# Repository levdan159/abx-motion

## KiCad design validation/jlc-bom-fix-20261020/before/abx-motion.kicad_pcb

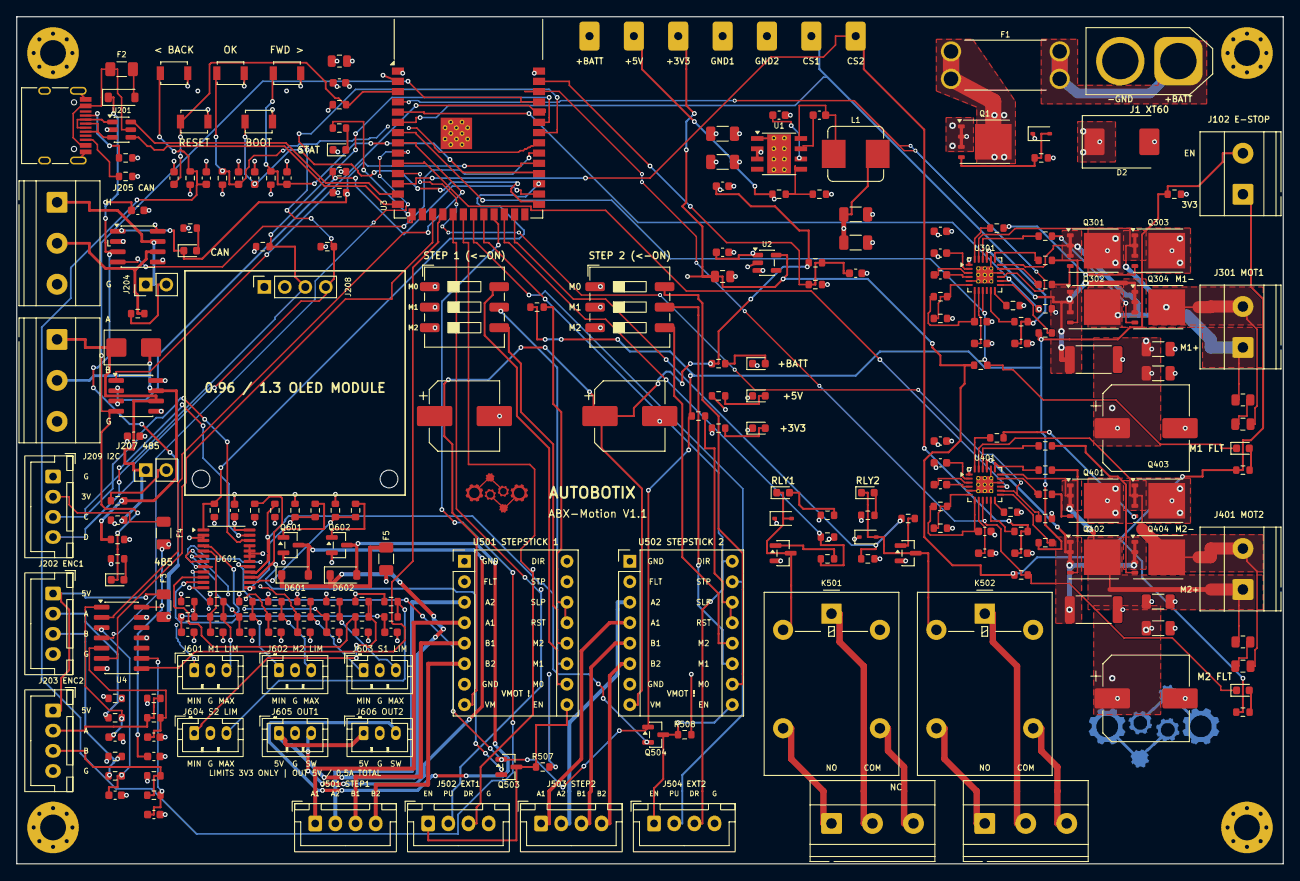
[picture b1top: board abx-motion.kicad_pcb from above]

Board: 4 copper layers, 157.0 x 105.0 mm, 250 parts (1 on the bottom side), 174 nets.

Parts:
C1, C4, C6, C202, C203, C204, C209, C210, C211, C212, C213, C214, C302, C309, C402, C409, C601: 100nF; C_0603_1608Metric
C2, C3, C307, C308, C407, C408: 4.7uF; C_1206_3216Metric
C5, C9, C301, C303, C304, C401, C403, C404: 1uF; C_0603_1608Metric
C7, C8: 22uF; C_1206_3216Metric
C10, C201: 10uF; C_0805_2012Metric
C205, C206, C207, C208: 1nF; C_0603_1608Metric
C305, C405, C602, C603, C604, C605, C606, C607, C608, C609: 10nF; C_0603_1608Metric
C306, C406: 220uF; CP_Elec_10x10.5
C310, C410: 2.2nF; C_0805_2012Metric
C501, C502: 100uF; CP_Elec_8x10.5
D1: BZT52C12S; D_SOD-323
D2: SMCJ30A; D_SMC
D201: SMBJ6.5CA; D_SMB
D202, D601, D602: B5819W; D_SOD-123
D501, D503: 1N4148WS; D_SOD-323
D502, D504: LED_GRN; LED_0603_1608Metric
F1: 25A; Fuseholder_Keystone_3557-2
F2, F3: 500mA_PTC; Fuse_1206_3216Metric
F4: 250mA_PTC; Fuse_1206_3216Metric
F5: 1206L050/15YR; Fuse_1206_3216Metric
H1, H2, H3, H4: M3_Mount; MountingHole_3.2mm_M3_Pad_Via
H5, H6: M2_OLED; MountingHole_2.2mm_M2
J1: XT60_BAT; AMASS_XT60-M_1x02_P7.20mm_Vertical
J102: E_STOP; TerminalBlock_Phoenix_MKDS-1,5-2-5.08_1x02_P5.08mm_Horizont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
J201: USB-C; USB_C_Receptacle_HRO_TYPE-C-31-M-12
J202: ENC1_CONN; JST_XH_B4B-XH-A_1x04_P2.50mm_Vertical
J203: ENC2_CONN; JST_XH_B4B-XH-A_1x04_P2.50mm_Vertical
J204: CAN_TERM; PinHeader_1x02_P2.54mm_Vertical
J205: CAN_BUS; TerminalBlock_Phoenix_MKDS-1,5-3-5.08_1x03_P5.08mm_Horizont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
J206: RS485_TERM; PinHeader_1x02_P2.54mm_Vertical
J207: RS485_BUS; TerminalBlock_Phoenix_MKDS-1,5-3-5.08_1x03_P5.08mm_Horizont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
J208: OLED_I2C; PinSocket_1x04_P2.54mm_Vertical
J209: I2C_EXP; JST_XH_B4B-XH-A_1x04_P2.50mm_Vertical
J301, J401: MOTOR_OUT; TerminalBlock_Phoenix_MKDS-1,5-2-5.08_1x02_P5.08mm_Horizont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
J501: STEP1_MOTOR; JST_XH_B4B-XH-A_1x04_P2.50mm_Vertical
J502: STEP1_EXT; JST_XH_B4B-XH-A_1x04_P2.50mm_Vertical
J503: STEP2_MOTOR; JST_XH_B4B-XH-A_1x04_P2.50mm_Vertical
J504: STEP2_EXT; JST_XH_B4B-XH-A_1x04_P2.50mm_Vertical
J505: RELAY1_OUT; TerminalBlock_Phoenix_MKDS-1,5-3-5.08_1x03_P5.08mm_Horizont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
J506: RELAY2_OUT; TerminalBlock_Phoenix_MKDS-1,5-3-5.08_1x03_P5.08mm_Horizont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
J601, J602, J603, J604, J605, J606: B3B-PH-K-S; JST_PH_B3B-PH-K_1x03_P2.00mm_Vertical
K501, K502: G5LE-14-DC5; Relay_SPDT_Omron-G5LE-1
L1: 15uH; L_Bourns_SRP7028A_7.3x6.6mm
LED201: LED_YEL_CAN; LED_0603_1608Metric
LED202: LED_YEL_485; LED_0603_1608Metric
LED203: LED_BLU_STAT; LED_0603_1608Metric
LED_FLT1, LED_FLT2: LED_RED_FLT; LED_0603_1608Metric
LED_PWR_3V3_1, LED_PWR_5V1: LED_GRN; LED_0603_1608Metric
LED_PWR_BATT1: LED_GRN; LED_0603_1608Metric
LOGO1: ABX_Logo_Gears_Gold
LOGO2: ABX_Text_Gold
Q1: SQJ459EP-T1_GE3; TDSON-8-1
Q301, Q302, Q303, Q304, Q401, Q402, Q403, Q404: CSD18540Q5B; TDSON-8-1
Q501, Q502, Q503, Q504, Q601, Q602: AO3400A; SOT-23
R1: 47k; R_0603_1608Metric
R2, R4: 100k; R_0603_1608Metric
R3, R6, R9, R203, R204, R205, R206, R207, R208, R209, R210, R227, R228, R229, R231, R232, R303, R403, R505, R506, R507, R508, R621, R622: 10k; R_0603_1608Metric
R5: 24.9k; R_0603_1608Metric
R7, R8, R212, R214, R216, R218, R220, R224, R230, R304, R311, R404, R411, R502, R504, R609, R610, R611, R612, R613, R614, R615, R616, R617, R618: 1k; R_0603_1608Metric
R201, R202: 5.1k; R_0603_1608Metric
R211, R213, R215, R217, R225, R226, R601, R602, R603, R604, R605, R606, R607, R608: 4.7k; R_0603_1608Metric
R219, R221: 120; R_0603_1608Metric
R222, R223: 330R; R_0603_1608Metric
R301, R401: 18k; R_0603_1608Metric
R302, R402: 30k; R_0603_1608Metric
R305, R306, R307, R308, R405, R406, R407, R408: 10; R_0603_1608Metric
R309, R409: 10mR_3W; R_2512_6332Metric
R310, R410: 10; R_0805_2012Metric
R312, R412: 200k; R_0603_1608Metric
R501, R503, R619, R620: 100; R_0603_1608Metric
SW201: RESET; SW_SPST_B3U-1000P
SW202: BOOT; SW_SPST_B3U-1000P
SW203: BTN_BACK; SW_SPST_B3U-1000P
SW204: BTN_NEXT; SW_SPST_B3U-1000P
SW205: BTN_HOME; SW_SPST_B3U-1000P
SW501, SW502: MICROSTEP_CFG; SW_DIP_SPSTx03_Slide_9.78x9.8mm_W8.61mm_P2.54mm
TP_3V3_1: TP_3V3_1; TestPoint_Pad_D1.5mm
TP_5V1: TP_5V1; TestPoint_Pad_D1.5mm
TP_BATT1: TP_BATT1; TestPoint_Pad_D1.5mm
TP_CS1, TP_CS2: TP_CS; TestPoint_Pad_D1.5mm
TP_GND1: TP_GND1; TestPoint_Pad_D1.5mm
TP_GND2: TP_GND2; TestPoint_Pad_D1.5mm
U1: LMR36520FADDA; Texas_HSOP-8-1EP_3.9x4.9mm_P1.27mm_ThermalVias
U2: AP2112K-3.3; SOT-23-5
U3: ESP32-S3-WROOM-1-N8R2; ESP32-S3-WROOM-1
U4: 74LVC14A; SOIC-14_3.9x8.7mm_P1.27mm
U201: USBLC6-2SC6; SOT-23-6
U202: TCAN1042V-Q1; SOIC-8_3.9x4.9mm_P1.27mm
U203: THVD1450DR; SOIC-8_3.9x4.9mm_P1.27mm
U301, U401: DRV8701ERGER; Texas_RGE0024C_VQFN-24-1EP_4x4mm_P0.5mm_EP2.1x2.1mm_Thermal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
U501, U502: StepStick_DRV8825; Pololu_Breakout-16_15.2x20.3mm
U601: PCA9555PW,118; TSSOP-24_4.4x7.8mm_P0.65mm

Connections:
+3V3: C10.1, C201.1, C202.1, C209.1, C211.1, C601.1, F4.1, J102.1, J208.2, R8.1, R203.1, R206.1, R209.1, R210.1, R220.1, R222.1, R224.1, R225.1, R226.1, R227.1, R228.1, R229.1, R232.1, R311.1, R411.1, R507.1, R508.1, R601.1, R602.1, R603.1, R604.1, R605.1, R606.1, R607.1, R608.1, R621.1, R622.1, SW501.1, SW501.2, SW501.3, SW502.1, SW502.2, SW502.3, TP_3V3_1.1 (1_1), U2.5 (VOUT), U3.2 (3V3), U4.14 (VCC), U202.5 (VIO), U203.8 (VCC), U601.24
+5V: C7.1, C8.1, C9.1, C210.1, D202.1 (K), D501.1 (K), D503.1 (K), F3.1, F5.1, K501.5, K502.5, L1.2, R4.1, R7.1, R211.1, R213.1, R215.1, R217.1, R502.1, R504.1, TP_5V1.1 (1_1), U2.1 (VIN), U2.3 (EN), U202.3 (VCC)
+BATT: C2.1, C3.1, C4.1, C301.1, C306.1, C307.1, C308.1, C309.1, C401.1, C406.1, C407.1, C408.1, C409.1, C501.1, C502.1, D1.1 (K), D2.1 (A1), Q1.1 (S), Q1.2 (S), Q1.3 (S), Q301.5 (D), Q303.5 (D), Q401.5 (D), Q403.5 (D), R2.1, R6.1, TP_BATT1.1 (1_1), U1.2 (VIN), U1.3 (EN), U301.1 (VM), U401.1 (VM), U501.8 (VMOT), U502.8 (VMOT)
/+3V3_DRV_EN: J102.2, Q503.1, Q504.1, R9.1, R303.1, R403.1, R505.1, R506.1, U601.17
/DC_Motor_1/DRV_AVDD: C303.1, R301.1, U301.7 (AVDD)
/DC_Motor_1/DRV_CPH: C302.1, U301.3 (CPH)
/DC_Motor_1/DRV_CPL: C302.2, U301.4 (CPL)
/DC_Motor_1/DRV_DVDD: C304.1, U301.8 (DVDD)
/DC_Motor_1/DRV_IDRIVE: R312.1, U301.12 (IDRIVE)
/DC_Motor_1/DRV_VCP: C301.2, U301.2 (VCP)
/DC_Motor_1/DRV_VREF: R301.2, R302.1, U301.6 (VREF)
/DC_Motor_1/DRV_nSLEEP: R303.2, U301.13 (nSLEEP)
/DC_Motor_1/FLT_LED_A: LED_FLT1.2 (A), R311.2
/DC_Motor_1/GH1_GATE: Q301.4 (G), R305.2
/DC_Motor_1/GH1_RAW: R305.1, U301.17 (GH1)
/DC_Motor_1/GH2_GATE: Q303.4 (G), R307.2
/DC_Motor_1/GH2_RAW: R307.1, U301.24 (GH2)
/DC_Motor_1/GL1_GATE: Q302.4 (G), R306.2
/DC_Motor_1/GL1_RAW: R306.1, U301.19 (GL1)
/DC_Motor_1/GL2_GATE: Q304.4 (G), R308.2
/DC_Motor_1/GL2_RAW: R308.1, U301.22 (GL2)
/DC_Motor_1/MOT_OUT1: J301.1, Q301.1 (S), Q301.2 (S), Q301.3 (S), Q302.5 (D), R310.1, U301.18 (SH1)
/DC_Motor_1/MOT_OUT2: C310.2, J301.2, Q303.1 (S), Q303.2 (S), Q303.3 (S), Q304.5 (D), U301.23 (SH2)
/DC_Motor_1/SHUNT_SP: Q302.1 (S), Q302.2 (S), Q302.3 (S), Q304.1 (S), Q304.2 (S), Q304.3 (S), R309.1, U301.21 (SP)
/DC_Motor_1/SNUB_MID: C310.1, R310.2
/DC_Motor_1/SO_RAW: R304.1, U301.11 (SO)
/DC_Motor_2/DRV_AVDD: C403.1, R401.1, U401.7 (AVDD)
/DC_Motor_2/DRV_CPH: C402.1, U401.3 (CPH)
/DC_Motor_2/DRV_CPL: C402.2, U401.4 (CPL)
/DC_Motor_2/DRV_DVDD: C404.1, U401.8 (DVDD)
/DC_Motor_2/DRV_IDRIVE: R412.1, U401.12 (IDRIVE)
/DC_Motor_2/DRV_VCP: C401.2, U401.2 (VCP)
/DC_Motor_2/DRV_VREF: R401.2, R402.1, U401.6 (VREF)
/DC_Motor_2/DRV_nSLEEP: R403.2, U401.13 (nSLEEP)
/DC_Motor_2/FLT_LED_A: LED_FLT2.2 (A), R411.2
/DC_Motor_2/GH1_GATE: Q401.4 (G), R405.2
/DC_Motor_2/GH1_RAW: R405.1, U401.17 (GH1)
/DC_Motor_2/GH2_GATE: Q403.4 (G), R407.2
/DC_Motor_2/GH2_RAW: R407.1, U401.24 (GH2)
/DC_Motor_2/GL1_GATE: Q402.4 (G), R406.2
/DC_Motor_2/GL1_RAW: R406.1, U401.19 (GL1)
/DC_Motor_2/GL2_GATE: Q404.4 (G), R408.2
/DC_Motor_2/GL2_RAW: R408.1, U401.22 (GL2)
/DC_Motor_2/MOT_OUT1: J401.1, Q401.1 (S), Q401.2 (S), Q401.3 (S), Q402.5 (D), R410.1, U401.18 (SH1)
/DC_Motor_2/MOT_OUT2: C410.2, J401.2, Q403.1 (S), Q403.2 (S), Q403.3 (S), Q404.5 (D), U401.23 (SH2)
/DC_Motor_2/SHUNT_SP: Q402.1 (S), Q402.2 (S), Q402.3 (S), Q404.1 (S), Q404.2 (S), Q404.3 (S), R409.1, U401.21 (SP)
/DC_Motor_2/SNUB_MID: C410.1, R410.2
/DC_Motor_2/SO_RAW: R404.1, U401.11 (SO)
/I2C_SCL: J208.3, J209.3, R225.2, U3.35 (IO42), U601.22
/I2C_SDA: J208.4, J209.4, R226.2, U3.34 (IO41), U601.23
/IO_INT_N: R206.2, U3.29 (IO36), U601.1
/Industrial_IO/+5V_OUT: D601.1, D602.1, F5.2, J605.1, J606.1
/Industrial_IO/M1_MAX_IN: C603.1, R610.2, U601.5
/Industrial_IO/M1_MAX_RAW: J601.3, R602.2, R610.1
/Industrial_IO/M1_MIN_IN: C602.1, R609.2, U601.4
/Industrial_IO/M1_MIN_RAW: J601.1, R601.2, R609.1
/Industrial_IO/M2_MAX_IN: C605.1, R612.2, U601.7
/Industrial_IO/M2_MAX_RAW: J602.3, R604.2, R612.1
/Industrial_IO/M2_MIN_IN: C604.1, R611.2, U601.6
/Industrial_IO/M2_MIN_RAW: J602.1, R603.2, R611.1
/Industrial_IO/OUT1_CMD: R617.1, R619.1, U601.13
/Industrial_IO/OUT1_GATE: Q601.1, R619.2
/Industrial_IO/OUT1_SW: D601.2, J605.3, Q601.3
/Industrial_IO/OUT2_CMD: R618.1, R620.1, U601.14
/Industrial_IO/OUT2_GATE: Q602.1, R620.2
/Industrial_IO/OUT2_SW: D602.2, J606.3, Q602.3
/Industrial_IO/S1_MAX_IN: C607.1, R614.2, U601.9
/Industrial_IO/S1_MAX_RAW: J603.3, R606.2, R614.1
/Industrial_IO/S1_MIN_IN: C606.1, R613.2, U601.8
/Industrial_IO/S1_MIN_RAW: J603.1, R605.2, R613.1
/Industrial_IO/S2_MAX_IN: C609.1, R616.2, U601.11
/Industrial_IO/S2_MAX_RAW: J604.3, R608.2, R616.1
/Industrial_IO/S2_MIN_IN: C608.1, R615.2, U601.10
/Industrial_IO/S2_MIN_RAW: J604.1, R607.2, R615.1
/M1_CS: C305.1, R304.2, TP_CS1.1 (1_1), U3.6 (IO6)
/M1_PWM_EN: R204.1, U3.5 (IO5), U301.14 (PH)
/M1_PWM_PH: U3.4 (IO4), U301.15 (EN)
/M1_nFAULT: LED_FLT1.1 (K), R209.2, U3.7 (IO7), U301.9 (nFAULT)
/M2_CS: C405.1, R404.2, TP_CS2.1 (1_1), U3.12 (IO8)
/M2_PWM_EN: R205.1, U3.11 (IO18), U401.14 (PH)
/M2_PWM_PH: U3.10 (IO17), U401.15 (EN)
/M2_nFAULT: LED_FLT2.1 (K), R210.2, U3.38 (IO2), U401.9 (nFAULT)
/MCU_and_Encoders/+3V3_EXT: F4.2, J209.2
/MCU_and_Encoders/+5V_ENC: F3.2, J202.1, J203.1
/MCU_and_Encoders/BTN_BACK: C212.1, R227.2, SW203.1, U3.23 (IO21)
/MCU_and_Encoders/BTN_HOME: C214.1, R229.2, SW205.1, U3.33 (IO40)
/MCU_and_Encoders/BTN_NEXT: C213.1, R228.2, SW204.1, U3.30 (IO37)
/MCU_and_Encoders/CAN_H: J204.1, J205.1, U202.7 (CANH)
/MCU_and_Encoders/CAN_L: J205.2, R219.2, U202.6 (CANL)
/MCU_and_Encoders/CAN_LED_A: LED201.2 (A), R220.2
/MCU_and_Encoders/CAN_RX: U3.32 (IO39), U202.4 (RXD)
/MCU_and_Encoders/CAN_TERM_SW: J204.2, R219.1
/MCU_and_Encoders/CAN_TX: LED201.1 (K), R232.2, U3.31 (IO38), U202.1 (TXD)
/MCU_and_Encoders/ENC1_A: U3.8 (IO15), U4.2
/MCU_and_Encoders/ENC1_A_FILT: C205.1, R212.2, U4.1
/MCU_and_Encoders/ENC1_A_RAW: J202.2, R211.2, R212.1
/MCU_and_Encoders/ENC1_B: U3.9 (IO16), U4.4
/MCU_and_Encoders/ENC1_B_FILT: C206.1, R214.2, U4.3
/MCU_and_Encoders/ENC1_B_RAW: J202.3, R213.2, R214.1
/MCU_and_Encoders/ENC2_A: U3.17 (IO9), U4.6
/MCU_and_Encoders/ENC2_A_FILT: C207.1, R216.2, U4.5
/MCU_and_Encoders/ENC2_A_RAW: J203.2, R215.2, R216.1
/MCU_and_Encoders/ENC2_B: U3.18 (IO10), U4.8
/MCU_and_Encoders/ENC2_B_FILT: C208.1, R218.2, U4.9
/MCU_and_Encoders/ENC2_B_RAW: J203.3, R217.2, R218.1
/MCU_and_Encoders/ESP_BOOT: C204.1, SW202.1, U3.27 (IO0)
/MCU_and_Encoders/ESP_EN: C203.1, R203.2, SW201.1, U3.3 (EN)
/MCU_and_Encoders/LED_STAT: R230.1, U3.15 (IO3)
/MCU_and_Encoders/RS485_A: D201.1 (A1), J206.1, J207.1, R222.2, U203.6 (A)
/MCU_and_Encoders/RS485_B: D201.2 (A2), J207.2, R221.2, R223.1, U203.7 (B)
/MCU_and_Encoders/RS485_DIR: R231.1, U3.28 (IO35), U203.2 (~RE), U203.3 (DE)
/MCU_and_Encoders/RS485_LED_A: LED202.2 (A), R224.2
/MCU_and_Encoders/RS485_RX: U3.36 (RXD0), U203.1 (RO)
/MCU_and_Encoders/RS485_TERM_SW: J206.2, R221.1
/MCU_and_Encoders/RS485_TX: LED202.1 (K), U3.37 (TXD0), U203.4 (DI)
/MCU_and_Encoders/STAT_LED_A: LED203.2 (A), R230.2
/MCU_and_Encoders/USB_CC1: J201.A5 (CC1), R201.1
/MCU_and_Encoders/USB_CC2: J201.B5 (CC2), R202.1
/MCU_and_Encoders/USB_CONN_DN: J201.A7 (D-), J201.B7 (D-), U201.1 (I/O1)
/MCU_and_Encoders/USB_CONN_DP: J201.A6 (D+), J201.B6 (D+), U201.3 (I/O2)
/MCU_and_Encoders/USB_DN: U3.13 (USB_D-), U201.6 (I/O1)
/MCU_and_Encoders/USB_DP: U3.14 (USB_D+), U201.4 (I/O2)
/MCU_and_Encoders/VBUS_FUSED: D202.2 (A), F2.2
/MCU_and_Encoders/VBUS_USB: F2.1, J201.A4 (VBUS), J201.A9 (VBUS), J201.B4 (VBUS), J201.B9 (VBUS), U201.5 (VBUS)
/Power_Supply/3V3_LED_A: LED_PWR_3V3_1.2 (A), R8.2
/Power_Supply/5V_LED_A: LED_PWR_5V1.2 (A), R7.2
/Power_Supply/BATT_LED_A: LED_PWR_BATT1.2 (A), R6.2
/Power_Supply/Q1_GATE: D1.2 (A), Q1.4 (G), R1.1
/Power_Supply/U1_BOOT: C6.1, U1.7 (BOOT)
/Power_Supply/U1_FB: R4.2, R5.1, U1.5 (FB)
/Power_Supply/U1_SW: C6.2, L1.1, U1.8 (SW)
/Power_Supply/U1_VCC: C5.1, U1.6 (VCC)
/Power_Supply/V_FUSED: F1.2, Q1.5 (D)
/Power_Supply/V_RAW_IN: F1.1, J1.1
/RELAY_1: R207.1, R501.1, U3.24 (IO47)
/RELAY_2: R208.1, R503.1, U3.25 (IO48)
/STEP1_DIR: J502.3, U3.20 (IO12), U501.16 (DIR)
/STEP1_EN: Q503.2, R621.2, U601.15
/STEP1_PUL: J502.2, U3.19 (IO11), U501.15 (STEP)
/STEP2_DIR: J504.3, U3.22 (IO14), U502.16 (DIR)
/STEP2_EN: Q504.2, R622.2, U601.16
/STEP2_PUL: J504.2, U3.21 (IO13), U502.15 (STEP)
/Steppers_and_Relays/RLY1_COIL_N: D501.2 (A), D502.1 (K), K501.2, Q501.3 (D)
/Steppers_and_Relays/RLY1_COM: J505.2, K501.1
/Steppers_and_Relays/RLY1_GATE: Q501.1 (G), R501.2
/Steppers_and_Relays/RLY1_LED_A: D502.2 (A), R502.2
/Steppers_and_Relays/RLY1_NC: J505.3, K501.4
/Steppers_and_Relays/RLY1_NO: J505.1, K501.3
/Steppers_and_Relays/RLY2_COIL_N: D503.2 (A), D504.1 (K), K502.2, Q502.3 (D)
/Steppers_and_Relays/RLY2_COM: J506.2, K502.1
/Steppers_and_Relays/RLY2_GATE: Q502.1 (G), R503.2
/Steppers_and_Relays/RLY2_LED_A: D504.2 (A), R504.2
/Steppers_and_Relays/RLY2_NC: J506.3, K502.4
/Steppers_and_Relays/RLY2_NO: J506.1, K502.3
/Steppers_and_Relays/STEP1_A1: J501.1, U501.4 (A1)
/Steppers_and_Relays/STEP1_A2: J501.2, U501.3 (A2)
/Steppers_and_Relays/STEP1_B1: J501.3, U501.5 (B1)
/Steppers_and_Relays/STEP1_B2: J501.4, U501.6 (B2)
/Steppers_and_Relays/STEP1_EN_GATED: J502.1, Q503.3, R507.2, U501.9 (~EN)
/Steppers_and_Relays/STEP1_M0: SW501.6, U501.10 (M0)
/Steppers_and_Relays/STEP1_M1: SW501.5, U501.11 (M1)
/Steppers_and_Relays/STEP1_M2: SW501.4, U501.12 (M2)
/Steppers_and_Relays/STEP1_nSLP_RST: R505.2, U501.13 (~RST), U501.14 (~SLP)
/Steppers_and_Relays/STEP2_A1: J503.1, U502.4 (A1)
/Steppers_and_Relays/STEP2_A2: J503.2, U502.3 (A2)
/Steppers_and_Relays/STEP2_B1: J503.3, U502.5 (B1)
/Steppers_and_Relays/STEP2_B2: J503.4, U502.6 (B2)
/Steppers_and_Relays/STEP2_EN_GATED: J504.1, Q504.3, R508.2, U502.9 (~EN)
/Steppers_and_Relays/STEP2_M0: SW502.6, U502.10 (M0)
/Steppers_and_Relays/STEP2_M1: SW502.5, U502.11 (M1)
/Steppers_and_Relays/STEP2_M2: SW502.4, U502.12 (M2)
/Steppers_and_Relays/STEP2_nSLP_RST: R506.2, U502.13 (~RST), U502.14 (~SLP)
/VBAT_SENSE: C1.1, R2.2, R3.1, U3.39 (IO1)
GND: C1.2, C2.2, C3.2, C4.2, C5.2, C7.2, C8.2, C9.2, C10.2, C201.2, C202.2, C203.2, C204.2, C205.2, C206.2, C207.2, C208.2, C209.2, C210.2, C211.2, C212.2, C213.2, C214.2, C303.2, C304.2, C305.2, C306.2, C307.2, C308.2, C309.2, C403.2, C404.2, C405.2, C406.2, C407.2, C408.2, C409.2, C501.2, C502.2, C601.2, C602.2, C603.2, C604.2, C605.2, C606.2, C607.2, C608.2, C609.2, D2.2 (A2), H1.1 (1_1), H2.1 (1_1), H3.1 (1_1), H4.1 (1_1), J1.2, J201.A1 (GND), J201.A12 (GND), J201.B1 (GND), J201.B12 (GND), J201.S1 (SHIELD), J202.4, J203.4, J205.3, J207.3, J208.1, J209.1, J502.4, J504.4, J601.2, J602.2, J603.2, J604.2, J605.2, J606.2, LED203.1 (K), LED_PWR_3V3_1.1 (K), LED_PWR_5V1.1 (K), LED_PWR_BATT1.1 (K), Q501.2 (S), Q502.2 (S), Q601.2, Q602.2, R1.2, R3.2, R5.2, R9.2, R201.2, R202.2, R204.2, R205.2, R207.2, R208.2, R223.2, R231.2, R302.2, R309.2, R312.2, R402.2, R409.2, R412.2, R617.2, R618.2, SW201.2, SW202.2, SW203.2, SW204.2, SW205.2, TP_GND1.1 (1_1), TP_GND2.1 (1_1), U1.1 (GND), U1.9 (GND), U2.2 (GND), U3.1 (GND), U3.40 (GND), U3.41 (GND), U4.7 (GND), U4.11, U4.13, U201.2 (GND), U202.2 (GND), U202.8 (STB), U203.5 (GND), U301.5 (AGND), U301.16 (PGND), U301.20 (SN), U301.25 (EP), U401.5 (AGND), U401.16 (PGND), U401.20 (SN), U401.25 (EP), U501.1 (GND), U501.7 (GND), U502.1 (GND), U502.7 (GND), U601.2, U601.3, U601.12, U601.18, U601.19, U601.20, U601.21

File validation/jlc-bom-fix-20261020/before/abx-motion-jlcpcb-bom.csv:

Comment,Designator,Footprint,LCSC Part #
10uF,"C10,C201",C_0805_2012Metric,C15850
1nF,"C205,C206,C207,C208",C_0603_1608Metric,C1588
100nF,"C1,C202,C203,C204,C209,C210,C211,C212,C213,C214,C302,C309,C4,C402,C409,C6,C601",C_0603_1608Metric,C14663
10nF,"C305,C405,C602,C603,C604,C605,C606,C607,C608,C609",C_0603_1608Metric,C57112
220uF,"C306,C406",CP_Elec_10x10.5,C72499
1uF,"C301,C303,C304,C401,C403,C404,C5,C9",C_0603_1608Metric,C15849
4.7uF,"C2,C3,C307,C308,C407,C408",C_1206_3216Metric,C29823
2.2nF,"C310,C410",C_0805_2012Metric,C107136
100uF,"C501,C502",CP_Elec_8x10.5,C72480
22uF,"C7,C8",C_1206_3216Metric,C12891
BZT52C12S,D1,D_SOD-323,C14643
SMCJ30A,D2,D_SMC,C310046
SMBJ6.5CA,D201,D_SMB,C78428
B5819W,"D202,D601,D602",D_SOD-123,C8598
1N4148WS,"D501,D503",D_SOD-323,C2128
LED_GRN,"D502,D504,LED_PWR_3V3_1,LED_PWR_5V1,LED_PWR_BATT1",LED_0603_1608Metric,C12624
25A,F1,Fuseholder_Keystone_3557-2,C352820
500mA_PTC,"F2,F3",Fuse_1206_3216Metric,C2984676
250mA_PTC,F4,Fuse_1206_3216Metric,C20798
1206L050/15YR,F5,Fuse_1206_3216Metric,C151162
XT60_BAT,J1,AMASS_XT60-M_1x02_P7.20mm_Vertical,C98733
E_STOP,J102,"TerminalBlock_Phoenix_MKDS-1,5-2-5.08_1x02_P5.08mm_Horizontal",C8465
USB-C,J201,USB_C_Receptacle_HRO_TYPE-C-31-M-12,C165948
ENC1_CONN,J202,JST_XH_B4B-XH-A_1x04_P2.50mm_Vertical,C566014
ENC2_CONN,J203,JST_XH_B4B-XH-A_1x04_P2.50mm_Vertical,C566014
CAN_TERM,J204,PinHeader_1x02_P2.54mm_Vertical,C492401
CAN_BUS,J205,"TerminalBlock_Phoenix_MKDS-1,5-3-5.08_1x03_P5.08mm_Horizontal",C72334
RS485_TERM,J206,PinHeader_1x02_P2.54mm_Vertical,C492401
RS485_BUS,J207,"TerminalBlock_Phoenix_MKDS-1,5-3-5.08_1x03_P5.08mm_Horizontal",C72334
OLED_I2C,J208,PinSocket_1x04_P2.54mm_Vertical,C2718488
I2C_EXP,J209,JST_XH_B4B-XH-A_1x04_P2.50mm_Vertical,C566014
MOTOR_OUT,"J301,J401","TerminalBlock_Phoenix_MKDS-1,5-2-5.08_1x02_P5.08mm_Horizontal",C8465
STEP1_MOTOR,J501,JST_XH_B4B-XH-A_1x04_P2.50mm_Vertical,C566014
STEP1_EXT,J502,JST_XH_B4B-XH-A_1x04_P2.50mm_Vertical,C566014
STEP2_MOTOR,J503,JST_XH_B4B-XH-A_1x04_P2.50mm_Vertical,C566014
STEP2_EXT,J504,JST_XH_B4B-XH-A_1x04_P2.50mm_Vertical,C566014
RELAY1_OUT,J505,"TerminalBlock_Phoenix_MKDS-1,5-3-5.08_1x03_P5.08mm_Horizontal",C72334
RELAY2_OUT,J506,"TerminalBlock_Phoenix_MKDS-1,5-3-5.08_1x03_P5.08mm_Horizontal",C72334
B3B-PH-K-S,"J601,J602,J603,J604,J605,J606",JST_PH_B3B-PH-K_1x03_P2.00mm_Vertical,C131339
G5LE-14-DC5,"K501,K502",Relay_SPDT_Omron-G5LE-1,C116963
15uH,L1,L_Bourns_SRP7028A_7.3x6.6mm,C177243
LED_YEL_CAN,LED201,LED_0603_1608Metric,C2287
LED_YEL_485,LED202,LED_0603_1608Metric,C2287
LED_BLU_STAT,LED203,LED_0603_1608Metric,C2288
LED_RED_FLT,"LED_FLT1,LED_FLT2",LED_0603_1608Metric,C2286
SQJ459EP-T1_GE3,Q1,TDSON-8-1,C3289501
CSD18540Q5B,"Q301,Q302,Q303,Q304,Q401,Q402,Q403,Q404",TDSON-8-1,C86513
AO3400A,"Q501,Q502,Q503,Q504,Q601,Q602",SOT-23,C20917
47k,R1,R_0603_1608Metric,C25819
100k,"R2,R4",R_0603_1608Metric,C25803
5.1k,"R201,R202",R_0603_1608Metric,C23186
120,"R219,R221",R_0603_1608Metric,C22787
330R,"R222,R223",R_0603_1608Metric,C23138
10k,"R203,R204,R205,R206,R207,R208,R209,R210,R227,R228,R229,R231,R232,R3,R303,R403,R505,R506,R507,R508,R6,R621,R622,R9",R_0603_1608Metric,C25804
18k,"R301,R401",R_0603_1608Metric,C25810
10mR_3W,"R309,R409",R_2512_6332Metric,C840621
10,"R310,R410",R_0805_2012Metric,C844598
200k,"R312,R412",R_0603_1608Metric,C25811
30k,"R302,R402",R_0603_1608Metric,C22984
1k,"R212,R214,R216,R218,R220,R224,R230,R304,R311,R404,R411,R502,R504,R609,R610,R611,R612,R613,R614,R615,R616,R617,R618,R7,R8",R_0603_1608Metric,C21190
10,"R305,R306,R307,R308,R405,R406,R407,R408",R_0603_1608Metric,C22859
24.9k,R5,R_0603_1608Metric,C25962
100,"R501,R503,R619,R620",R_0603_1608Metric,C22775
4.7k,"R211,R213,R215,R217,R225,R226,R601,R602,R603,R604,R605,R606,R607,R608",R_0603_1608Metric,C23162
RESET,SW201,SW_SPST_B3U-1000P,C231329
BOOT,SW202,SW_SPST_B3U-1000P,C231329
BTN_BACK,SW203,SW_SPST_B3U-1000P,C231329
BTN_NEXT,SW204,SW_SPST_B3U-1000P,C231329
BTN_HOME,SW205,SW_SPST_B3U-1000P,C231329
MICROSTEP_CFG,"SW501,SW502",SW_DIP_SPSTx03_Slide_9.78x9.8mm_W8.61mm_P2.54mm,C319040
LMR36520FADDA,U1,Texas_HSOP-8-1EP_3.9x4.9mm_P1.27mm_ThermalVias,C1858395
AP2112K-3.3,U2,SOT-23-5,C51118
USBLC6-2SC6,U201,SOT-23-6,C7519
TCAN1042V-Q1,U202,SOIC-8_3.9x4.9mm_P1.27mm,C132550
THVD1450DR,U203,SOIC-8_3.9x4.9mm_P1.27mm,C2671361
ESP32-S3-WROOM-1-N8R2,U3,ESP32-S3-WROOM-1,C2913204
DRV8701ERGER,"U301,U401",Texas_RGE0024C_VQFN-24-1EP_4x4mm_P0.5mm_EP2.1x2.1mm_ThermalVias,C90964
74LVC14A,U4,SOIC-14_3.9x8.7mm_P1.27mm,C133541
PinSocket_1x08,"U501_L,U501_R,U502_L,U502_R",PinSocket_1x08_P2.54mm_Vertical,C145755
"PCA9555PW,118",U601,TSSOP-24_4.4x7.8mm_P0.65mm,C128392

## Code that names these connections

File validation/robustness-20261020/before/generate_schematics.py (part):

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    sb.stub_net(u3, "27", "ESP_BOOT", length=7.62)
    sb.stub_net(u3, "39", "VBAT_SENSE", length=7.62, hier_shape="input")
    sb.stub_net(u3, "38", "M2_nFAULT", length=7.62, hier_shape="input")
    sb.stub_net(u3, "15", "LED_STAT", length=7.62)  # GPIO 3 Heartbeat LED
    sb.stub_net(u3, "4", "M1_PWM_PH", length=7.62, hier_shape="output")
    sb.stub_net(u3, "5", "M1_PWM_EN", length=7.62, hier_shape="output")
    sb.stub_net(u3, "6", "M1_CS", length=7.62, hier_shape="input")
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    sb.stub_net(u3, "9", "ENC1_B", length=7.62)

    # Right side pins of U3 (All expansion pins connected!)
    sb.stub_net(u3, "37", "RS485_TX", length=7.62)      # GPIO 43 (TXD0)
    sb.stub_net(u3, "36", "RS485_RX", length=7.62)      # GPIO 44 (RXD0)
    sb.stub_net(u3, "10", "M2_PWM_PH", length=7.62, hier_shape="output")
    sb.stub_net(u3, "11", "M2_PWM_EN", length=7.62, hier_shape="output")
    sb.stub_net(u3, "13", "USB_DN", length=7.62)
    sb.stub_net(u3, "14", "USB_DP", length=7.62)
    sb.stub_net(u3, "23", "BTN_BACK", length=7.62)      # GPIO 21 (moved from GPIO 36)
    sb.stub_net(u3, "28", "RS485_DIR", length=7.62)     # GPIO 35
    sb.stub_net(u3, "29", "IO_INT_N", length=7.62, hier_shape="input")  # GPIO 36 (~INT from PCA9555PW)
    sb.stub_net(u3, "30", "BTN_NEXT", length=7.62)      # GPIO 37
    sb.stub_net(u3, "31", "CAN_TX", length=7.62)        # GPIO 38
    sb.stub_net(u3, "32", "CAN_RX", length=7.62)        # GPIO 39
    sb.stub_net(u3, "33", "BTN_HOME", length=7.62)      # GPIO 40
    sb.stub_net(u3, "34", "I2C_SDA", length=7.62, hier_shape="bidirectional")  # GPIO 41
    sb.stub_net(u3, "35", "I2C_SCL", length=7.62, hier_shape="output")         # GPIO 42
    sb.no_conn(u3, "26")                                # IO45 strapping pin unused
    sb.no_conn(u3, "16")                                # IO46 strapping pin unused
    sb.stub_net(u3, "24", "RELAY_1", length=7.62, hier_shape="output")
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    for gpin in ["S1", "A1", "A12", "B1", "B12"]:
        sb.stub_power(j201, gpin, "GND")
    for vpin in ["A4", "A9", "B4", "B9"]:
        sb.stub_net(j201, vpin, "VBUS_USB", length=6.35)
    sb.stub_net(j201, "A5", "USB_CC1", length=6.35)
    sb.stub_net(j201, "B5", "USB_CC2", length=6.35)
    sb.stub_net(j201, "A7", "USB_CONN_DN", length=6.35)
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    sb.stub_net(r219, "1", "CAN_TERM_SW")
    sb.stub_net(r219, "2", "CAN_L")

    # CAN 3-Pin 5.08mm Terminal J205 (CAN_H, CAN_L, GND)
    j205 = sb.place_sym(
        "Connector:Conn_01x03_Pin",
        "J205",
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    sb.stub_net(r223, "1", "RS485_B")
    sb.stub_power(r223, "2", "GND")

    # TVS Diode D201 across RS485_A and RS485_B + 3-Pin 5.08mm Terminal J207 (A, B, GND)
    d201 = sb.place_sym("Device:D_TVS", "D201", "SMBJ6.5CA", "Diode_SMD:D_SMB", 241.3, 264.16, 90)
    sb.stub_net(d201, "1", "RS485_A")
    sb.stub_net(d201, "2", "RS485_B")
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        sb.stub_net(sw_b, "1", btn_net)
        sb.stub_power(sw_b, "2", "GND")

    # 5. Heartbeat LED203 (Blue) + 1k Resistor R230 on GPIO 3 (LED_STAT)
    r230 = sb.place_sym("Device:R", "R230", "1k", "Resistor_SMD:R_0603_1608Metric", 35.56, 185.42, 0)
    sb.stub_net(r230, "1", "LED_STAT")
    sb.stub_net(r230, "2", "STAT_LED_A")
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    sb.stub_net(udrv, "12", "DRV_IDRIVE", length=7.62)  # Configurable IDRIVE via 200k R312/R412 to GND
    sb.stub_power(udrv, "5", "GND", length=7.62)   # AGND

    # R12 (R312 / R412): 200k 0603 from DRV_IDRIVE (Pin 12) to GND -> 25mA/50mA gate drive & bench-tunable
    r, alt = mref("R12")
    r_idrv = sb.place_sym("Device:R", r, "200k", "Resistor_SMD:R_0603_1608Metric", 198.12, 175.26, 0, alt_refs=alt)
    sb.stub_net(r_idrv, "1", "DRV_IDRIVE")
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    sb.stub_net(udrv, "24", "GH2_RAW", length=7.62)
    sb.stub_net(udrv, "23", "MOT_OUT2", length=7.62)
    sb.stub_net(udrv, "22", "GL2_RAW", length=7.62)
    sb.stub_net(udrv, "21", "SHUNT_SP", length=7.62)  # Pin 21 (SP) -> low-side MOSFET source node (top of R309)
    sb.stub_power(udrv, "20", "GND", length=7.62)     # Pin 20 (SN) -> GND Kelvin side of R309
    sb.stub_net(udrv, "11", "SO_RAW", length=7.62)
    sb.stub_net(udrv, "9", "nFAULT", length=7.62, hier_shape="output")
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        sb.stub_power(j_out, "2", "GND")
        sb.stub_net(j_out, "3", f"OUT{ch}_SW")

    # 4. Independent Stepper Enables (IO1_2=Pin 15 -> STEP1_EN, IO1_3=Pin 16 -> STEP2_EN) with 10k pull-ups R621, R622 to +3V3 & ESTOP_SENSE (IO1_4=Pin 17)
    sb.stub_net(u601, "15", "STEP1_EN", length=7.62, hier_shape="output")
    sb.stub_net(u601, "16", "STEP2_EN", length=7.62, hier_shape="output")

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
